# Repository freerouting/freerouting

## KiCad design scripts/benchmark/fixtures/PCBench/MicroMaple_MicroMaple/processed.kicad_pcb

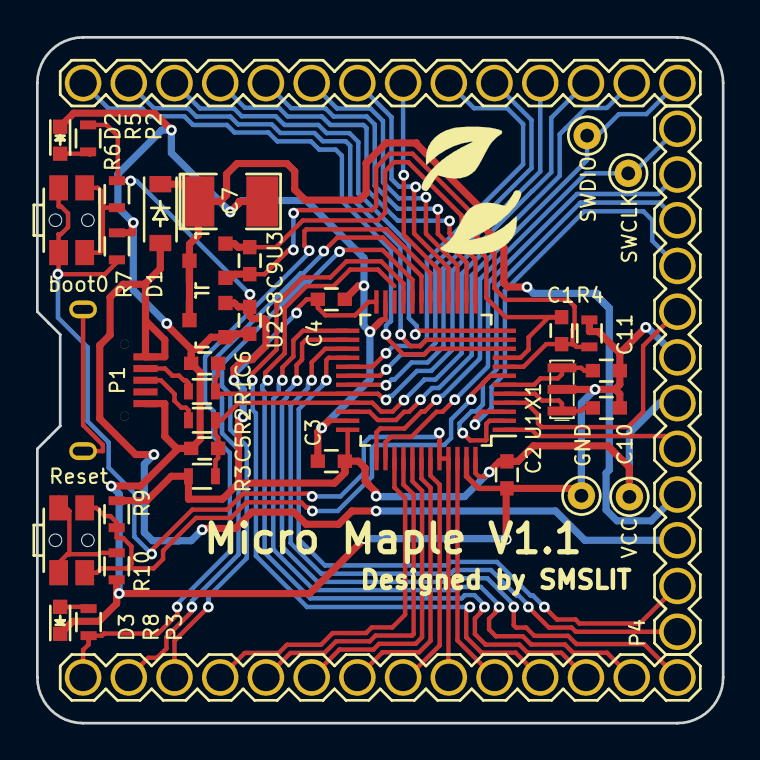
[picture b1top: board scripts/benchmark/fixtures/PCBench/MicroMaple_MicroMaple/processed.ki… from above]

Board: 2 copper layers, 38.1 x 38.1 mm, 38 parts (0 on the bottom side), 51 nets.

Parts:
C1, C2, C3, C4: 1uF; C_0603
C5, C6: 47pF; C_0603
C7: 100uF; SMD-1210_Pol
C8, C9: 10uF; C_0603
C10, C11: 18pF; C_0603
D1: D_Small; SOD-123
D2: PWR; LED_0603
D3: GREEN; LED_0603
P1: USB_OTG; USB_Micro-B-MK5
P2, P3: CONN_01X14; Connector_FAD_14x1
P4: CONN_01X12; Connector_FAD_12x1
P5, P6, P7, P8: CONN_01X01; Debug_Pin_1
R1, R2: 22; R_0603
R3: 1.5K; R_0603
R4: 0; R_0603
R5, R6, R8, R10: 1K; R_0603
R7, R9: 10K; R_0603
SW1: USR_BUT; SW_SPST_EVQP7C
SW2: RST_BUTTON; SW_SPST_EVQP7C
U1: STM32F103C8T6; LQFP-48_7x7mm_Pitch0.5mm
U2, U3: XC6206P332MR; SOT-23
X1: 8MHz_OSC; Resonator_3.2x1.5mm

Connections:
+5V: D1.2, P1.1, P4.10
+BATT: C7.1, D1.1, P4.9, U2.3, U3.3
/OSC_IN: C10.2, U1.5, X1.1
/OSC_OUT: C11.2, U1.6, X1.2
/PA0: P2.1, U1.10
/PA1: P2.2, U1.11
/PA2: P2.3, U1.12
/PA3: P2.4, U1.13
/PA4: P2.5, U1.14
/PA5: P2.6, U1.15
/PA6: P2.7, U1.16
/PA7: P2.8, U1.17
/PA8: P2.9, U1.29
/PA9: P2.10, U1.30
/PA10: P2.11, U1.31
/PA11: C6.1, P2.12, R1.1, U1.32
/PA12: C5.1, P2.13, R2.1, R3.1, U1.33
/PA13: P2.14, P5.1, U1.34
/PA14: P4.1, P6.1, U1.37
/PA15: P4.2, U1.38
/PB0: P3.1, R8.2, U1.18
/PB1: P3.2, U1.19
/PB2: P3.3, U1.20
/PB3: P3.4, U1.39
/PB4: P3.5, U1.40
/PB5: P3.6, U1.41
/PB6: P3.7, U1.42
/PB7: P3.8, U1.43
/PB8: P3.9, R7.2, SW1.2, U1.44, U1.45
/PB9: P3.10, U1.46
/PB10: P3.11, U1.21
/PB11: P3.12, U1.22
/PB12: P3.13, U1.25
/PB13: P3.14, U1.26
/PB14: P4.12, U1.27
/PB15: P4.11, U1.28
/PC13: P4.3, U1.2
/PC14: P4.4, U1.3
/PC15: P4.5, U1.4
/RST: R9.1, SW2.1, U1.7
/VBAT: P4.8, U1.1
GND: C2.2, C3.2, C4.2, C5.2, C6.2, C7.2, C8.2, C10.1, C11.1, D2.1, D3.1, P1.5, P4.6, P8.1, R4.1, R7.1, R10.2, U1.23, U1.35, U1.47, U2.1, X1.3
GNDA: C1.1, C9.2, R4.2, U1.8, U3.1
unnamed: D2.2, R5.1
unnamed: D3.2, R8.1
unnamed: P1.2, R1.2
unnamed: P1.3, R2.2
unnamed: R6.2, SW1.1
unnamed: R10.1, SW2.2
VCC: C2.1, C3.1, C4.1, C8.1, P4.7, P7.1, R3.2, R5.2, R6.1, R9.2, U1.24, U1.36, U1.48, U2.2
VDDA: C1.2, C9.1, U1.9, U3.2

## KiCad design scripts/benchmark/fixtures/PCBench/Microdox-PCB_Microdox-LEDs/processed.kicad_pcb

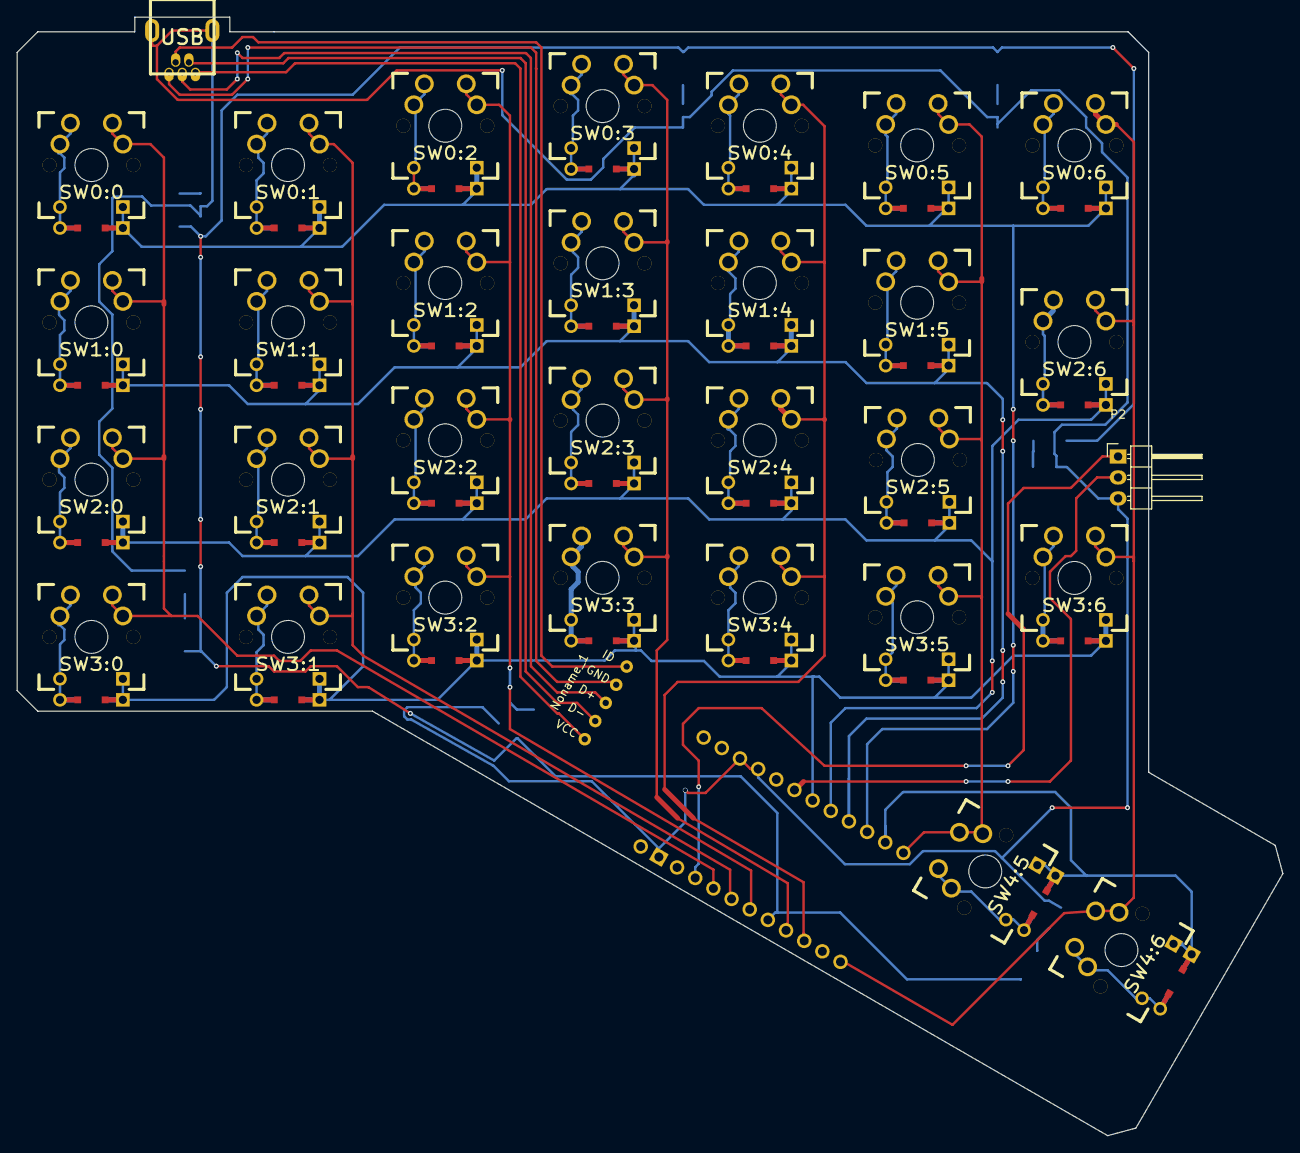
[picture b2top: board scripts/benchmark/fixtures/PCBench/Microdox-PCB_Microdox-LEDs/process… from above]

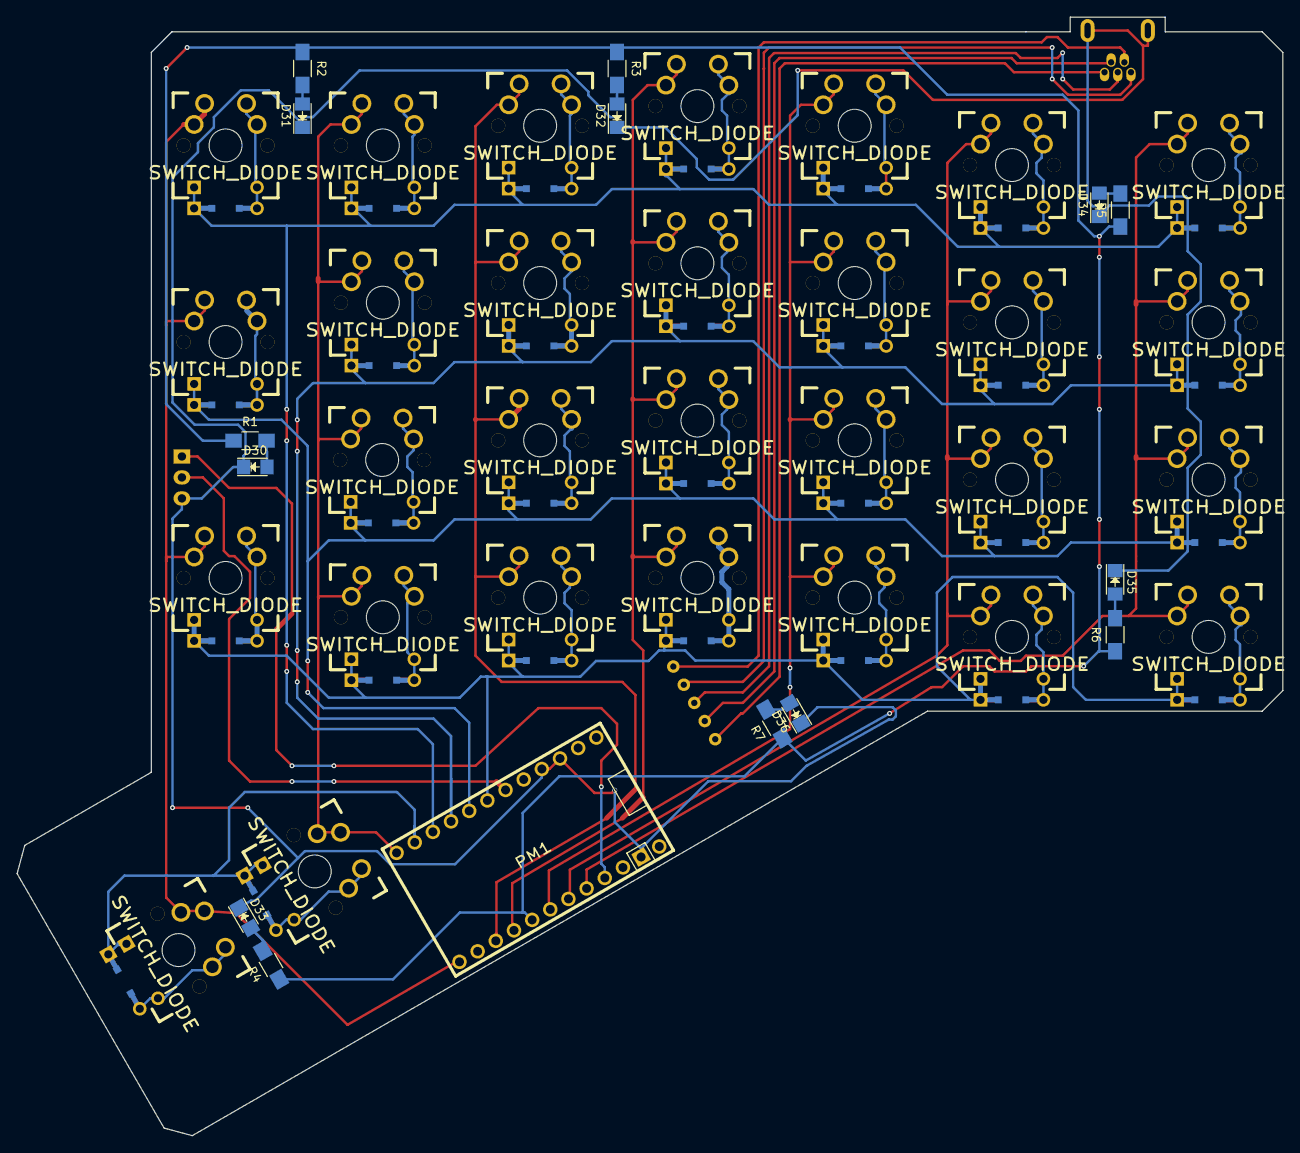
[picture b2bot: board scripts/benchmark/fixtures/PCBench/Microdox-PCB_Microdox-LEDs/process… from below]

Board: 2 copper layers, 153.3 x 135.5 mm, 47 parts (15 on the bottom side), 57 nets.

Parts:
D30, D31, D32, D33, D34, D35, D36: LED; LED_1206
Noname_1: USBWirePins
P1: USB; USBMINI
P2: CONN_01X03; Pin_Header_Angled_1x03
PM1: PROMICRO
R1, R2, R3, R4, R5, R6, R7: 100R; R_1206_HandSoldering
SW0:0, SW0:1, SW0:2, SW0:3, SW0:4, SW0:5, SW0:6, SW1:0, SW1:1, SW1:2, SW1:3, SW1:4, SW1:5, SW2:0, SW2:1, SW2:2, SW2:3, SW2:4, SW2:5, SW2:6, SW3:0, SW3:1, SW3:2, SW3:3, SW3:4, SW3:5, SW3:6, SW4:5, SW4:6: SWITCH_DIODE; MX_FLIP_DIODE

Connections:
/COL0: PM1.16, SW0:0.1, SW1:0.1, SW2:0.1, SW3:0.1
/COL1: PM1.17, SW0:1.1, SW1:1.1, SW2:1.1, SW3:1.1
/COL2: PM1.18, SW0:2.1, SW1:2.1, SW2:2.1, SW3:2.1
/COL3: PM1.20, SW0:3.1, SW1:3.1, SW2:3.1, SW3:3.1
/COL4: PM1.21, SW0:4.1, SW1:4.1, SW2:4.1, SW3:4.1
/COL5: PM1.11, SW0:5.1, SW1:5.1, SW2:5.1, SW3:5.1, SW4:5.1
/COL6: PM1.23, SW0:6.1, SW2:6.1, SW3:6.1, SW4:6.1
/LED+: PM1.19, R1.1, R2.1, R3.1, R4.1, R5.1, R6.1, R7.1
/ROW0: PM1.9, SW0:0.4, SW0:1.4, SW0:2.4, SW0:3.4, SW0:4.4, SW0:5.4, SW0:6.4
/ROW1: PM1.8, SW1:0.4, SW1:1.4, SW1:2.4, SW1:3.4, SW1:4.4, SW1:5.4
/ROW2: PM1.7, SW2:0.4, SW2:1.4, SW2:2.4, SW2:3.4, SW2:4.4, SW2:5.4, SW2:6.4
/ROW3: PM1.6, SW3:0.4, SW3:1.4, SW3:2.4, SW3:3.4, SW3:4.4, SW3:5.4, SW3:6.4
/ROW4: PM1.10, SW4:5.4, SW4:6.4
/SER: P2.2, PM1.5
GND: D30.1, D31.1, D32.1, D33.1, D34.1, D35.1, D36.1, P1.6, P2.3, PM1.2, PM1.3, PM1.13
unnamed: D30.2, R1.2
unnamed: D31.2, R2.2
unnamed: D32.2, R3.2
unnamed: D33.2, R4.2
unnamed: D34.2, R5.2
unnamed: D35.2, R6.2
unnamed: D36.2, R7.2
unnamed: Noname_1.1, P1.1
unnamed: Noname_1.2, P1.2
unnamed: Noname_1.3, P1.3
unnamed: Noname_1.4, P1.4
unnamed: Noname_1.5, P1.5
unnamed: SW0:0.2, SW0:0.3
unnamed: SW0:1.2, SW0:1.3
unnamed: SW0:2.2, SW0:2.3
unnamed: SW0:3.2, SW0:3.3
unnamed: SW0:4.2, SW0:4.3
unnamed: SW0:5.2, SW0:5.3
unnamed: SW0:6.2, SW0:6.3
unnamed: SW1:0.2, SW1:0.3
unnamed: SW1:1.2, SW1:1.3
unnamed: SW1:2.2, SW1:2.3
unnamed: SW1:3.2, SW1:3.3
unnamed: SW1:4.2, SW1:4.3
unnamed: SW1:5.2, SW1:5.3
unnamed: SW2:0.2, SW2:0.3
unnamed: SW2:1.2, SW2:1.3
unnamed: SW2:2.2, SW2:2.3
unnamed: SW2:3.2, SW2:3.3
unnamed: SW2:4.2, SW2:4.3
unnamed: SW2:5.2, SW2:5.3
unnamed: SW2:6.2, SW2:6.3
unnamed: SW3:0.2, SW3:0.3
unnamed: SW3:1.2, SW3:1.3
unnamed: SW3:2.2, SW3:2.3
unnamed: SW3:3.2, SW3:3.3
unnamed: SW3:4.2, SW3:4.3
unnamed: SW3:5.2, SW3:5.3
unnamed: SW3:6.2, SW3:6.3
unnamed: SW4:5.2, SW4:5.3
unnamed: SW4:6.2, SW4:6.3
VCC: P2.1, PM1.15
